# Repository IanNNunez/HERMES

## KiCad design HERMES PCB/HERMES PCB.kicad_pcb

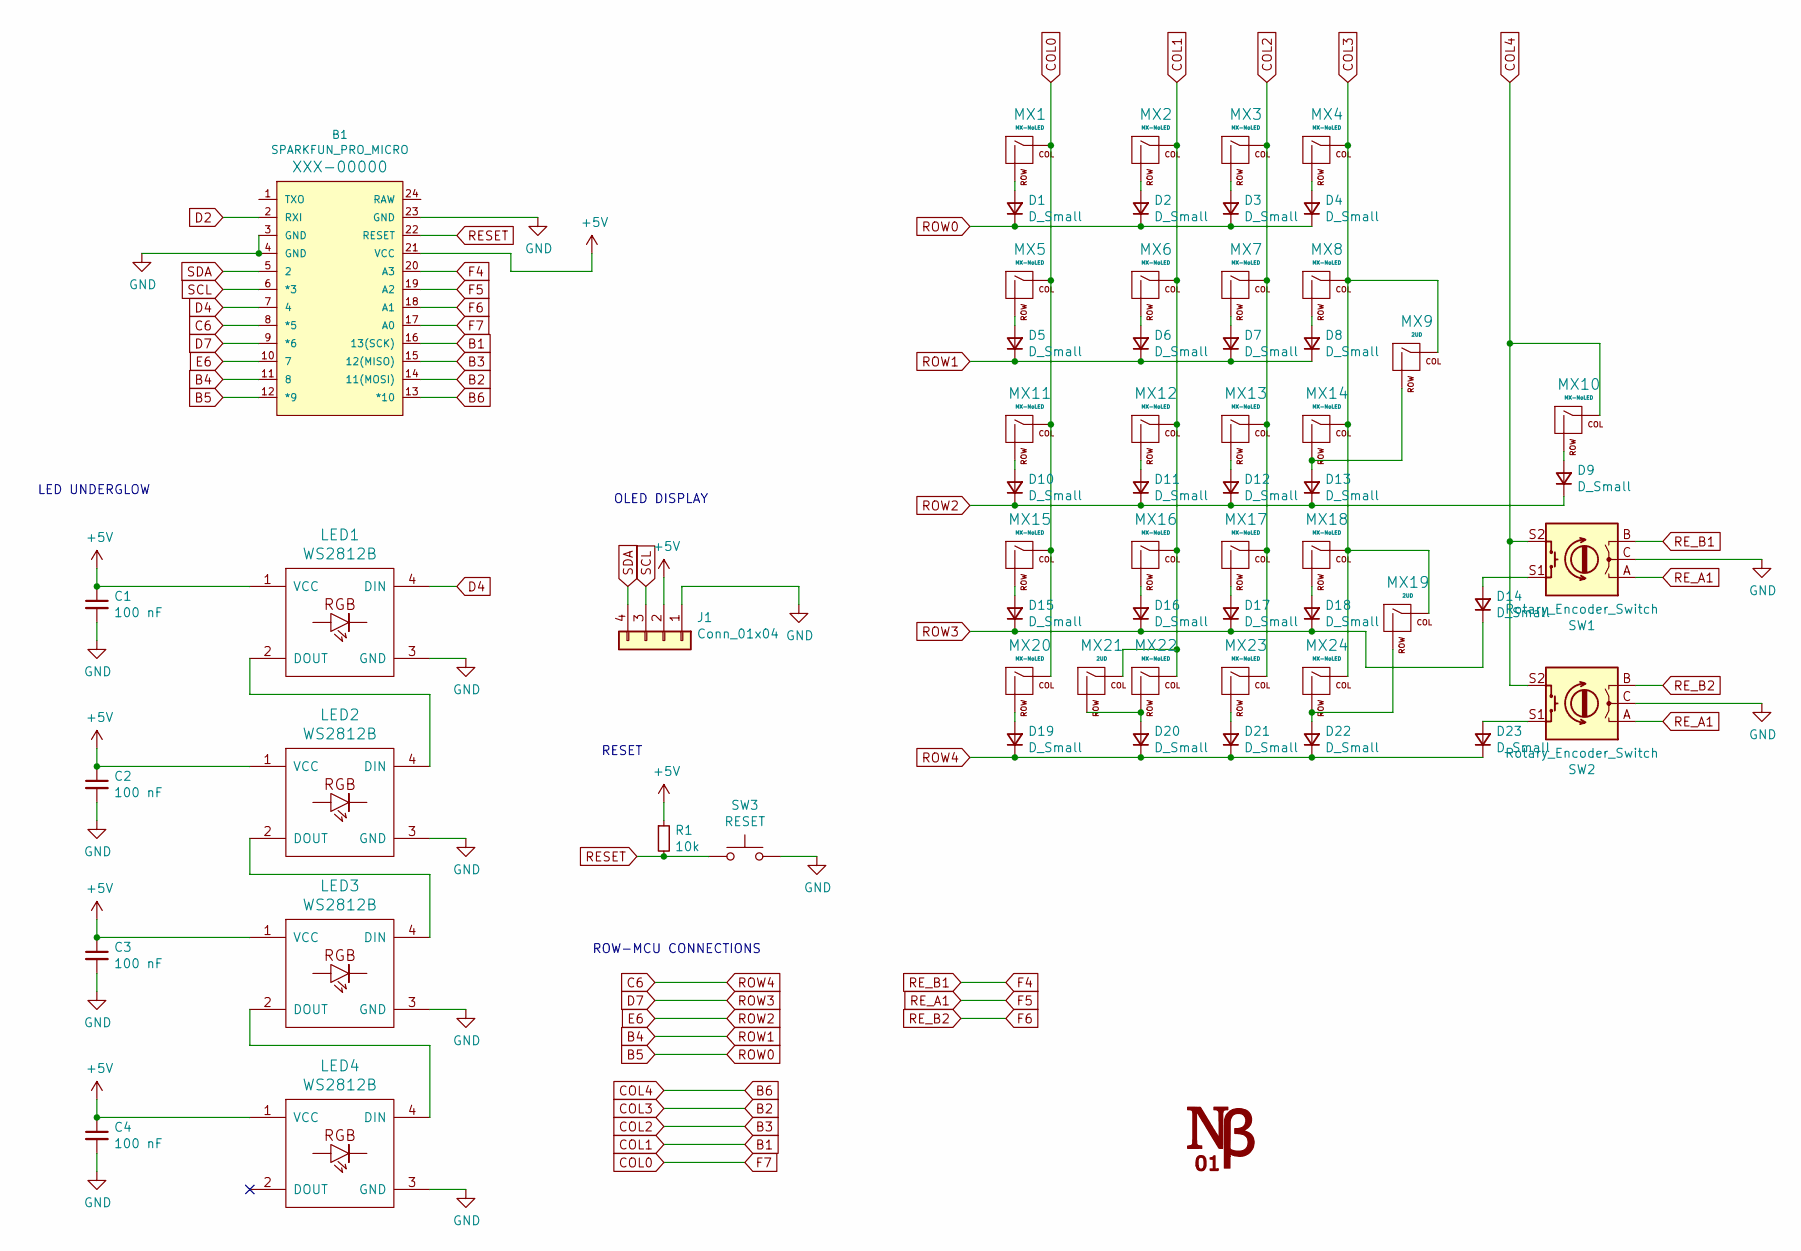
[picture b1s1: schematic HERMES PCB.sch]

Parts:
B1: SPARKFUN_PRO_MICRO
C1, C2, C3, C4: 100 nF; C_Disc_D3.0mm_W1.6mm_P2.50mm
D1, D2, D3, D4, D5, D6, D7, D8, D9, D10, D11, D12, D13, D14, D15, D16, D17, D18, D19, D20, D21, D22, D23: D_Small; D_DO-35_SOD27_P7.62mm_Horizontal
J1: Conn_01x04; PinHeader_1x04_P1.00mm_Vertical
LED1, LED2, LED3, LED4: WS2812B; LED_WS2812B_PLCC4_5.0x5.0mm_P3.2mm
MX1, MX2, MX3, MX4, MX5, MX6, MX7, MX8, MX10, MX11, MX12, MX13, MX14, MX15, MX16, MX17, MX18, MX20, MX22, MX23, MX24: MX-NoLED; MXOnly-1U-NoLED
MX9, MX19, MX21: 2UD; MXOnly-1U-NoLED
R1: 10k; R_Axial_DIN0204_L3.6mm_D1.6mm_P7.62mm_Horizontal
SW1, SW2: Rotary_Encoder_Switch; RotaryEncoder_Alps_EC11E-Switch_Vertical_H20mm
SW3: RESET; PushButton_6x6mm_TH

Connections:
+5V: B1.21 (VCC), C1.1, C2.1, C3.1, C4.1, J1.2, LED1.1 (VCC), LED2.1 (VCC), LED3.1 (VCC), LED4.1 (VCC), R1.1
B1: B1.16 (13(SCK)), MX2.1 (COL), MX6.1 (COL), MX12.1 (COL), MX16.1 (COL), MX21.1 (COL), MX22.1 (COL)
B2: B1.14 (11(MOSI)), MX4.1 (COL), MX8.1 (COL), MX9.1 (COL), MX14.1 (COL), MX18.1 (COL), MX19.1 (COL), MX24.1 (COL)
B3: B1.15 (12(MISO)), MX3.1 (COL), MX7.1 (COL), MX13.1 (COL), MX17.1 (COL), MX23.1 (COL)
B4: B1.11 (8), D5.1 (K), D6.1 (K), D7.1 (K), D8.1 (K)
B5: B1.12 (*9), D1.1 (K), D2.1 (K), D3.1 (K), D4.1 (K)
B6: B1.13 (*10), MX10.1 (COL), SW1.S2, SW2.S2
C6: B1.8 (*5), D19.1 (K), D20.1 (K), D21.1 (K), D22.1 (K), D23.1 (K)
COL0: B1.17 (A0), MX1.1 (COL), MX5.1 (COL), MX11.1 (COL), MX15.1 (COL), MX20.1 (COL)
D2: B1.2 (RXI)
D4: B1.7 (4), LED1.4 (DIN)
D7: B1.9 (*6), D14.1 (K), D15.1 (K), D16.1 (K), D17.1 (K), D18.1 (K)
E6: B1.10 (7), D9.1 (K), D10.1 (K), D11.1 (K), D12.1 (K), D13.1 (K)
F4: B1.20 (A3), SW1.B
F5: B1.19 (A2), SW1.A, SW2.A
F6: B1.18 (A1), SW2.B
GND: B1.3 (GND), B1.4 (GND), B1.23 (GND), C1.2, C2.2, C3.2, C4.2, J1.1, LED1.3 (GND), LED2.3 (GND), LED3.3 (GND), LED4.3 (GND), SW1.C, SW2.C, SW3.2
unnamed: D1.2 (A), MX1.2 (ROW)
unnamed: D2.2 (A), MX2.2 (ROW)
unnamed: D3.2 (A), MX3.2 (ROW)
unnamed: D4.2 (A), MX4.2 (ROW)
unnamed: D5.2 (A), MX5.2 (ROW)
unnamed: D6.2 (A), MX6.2 (ROW)
unnamed: D7.2 (A), MX7.2 (ROW)
unnamed: D8.2 (A), MX8.2 (ROW)
unnamed: D9.2 (A), MX10.2 (ROW)
unnamed: D10.2 (A), MX11.2 (ROW)
unnamed: D11.2 (A), MX12.2 (ROW)
unnamed: D12.2 (A), MX13.2 (ROW)
unnamed: D13.2 (A), MX9.2 (ROW), MX14.2 (ROW)
unnamed: D14.2 (A), SW1.S1
unnamed: D15.2 (A), MX15.2 (ROW)
unnamed: D16.2 (A), MX16.2 (ROW)
unnamed: D17.2 (A), MX17.2 (ROW)
unnamed: D18.2 (A), MX18.2 (ROW)
unnamed: D19.2 (A), MX20.2 (ROW)
unnamed: D20.2 (A), MX21.2 (ROW), MX22.2 (ROW)
unnamed: D21.2 (A), MX23.2 (ROW)
unnamed: D22.2 (A), MX19.2 (ROW), MX24.2 (ROW)
unnamed: D23.2 (A), SW2.S1
unnamed: LED1.2 (DOUT), LED2.4 (DIN)
unnamed: LED2.2 (DOUT), LED3.4 (DIN)
unnamed: LED3.2 (DOUT), LED4.4 (DIN)
RESET: B1.22 (RESET), R1.2, SW3.1
SCL: B1.6 (*3), J1.3
SDA: B1.5 (2), J1.4

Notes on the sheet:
LED UNDERGLOW
OLED DISPLAY
RESET
ROW-MCU CONNECTIONS

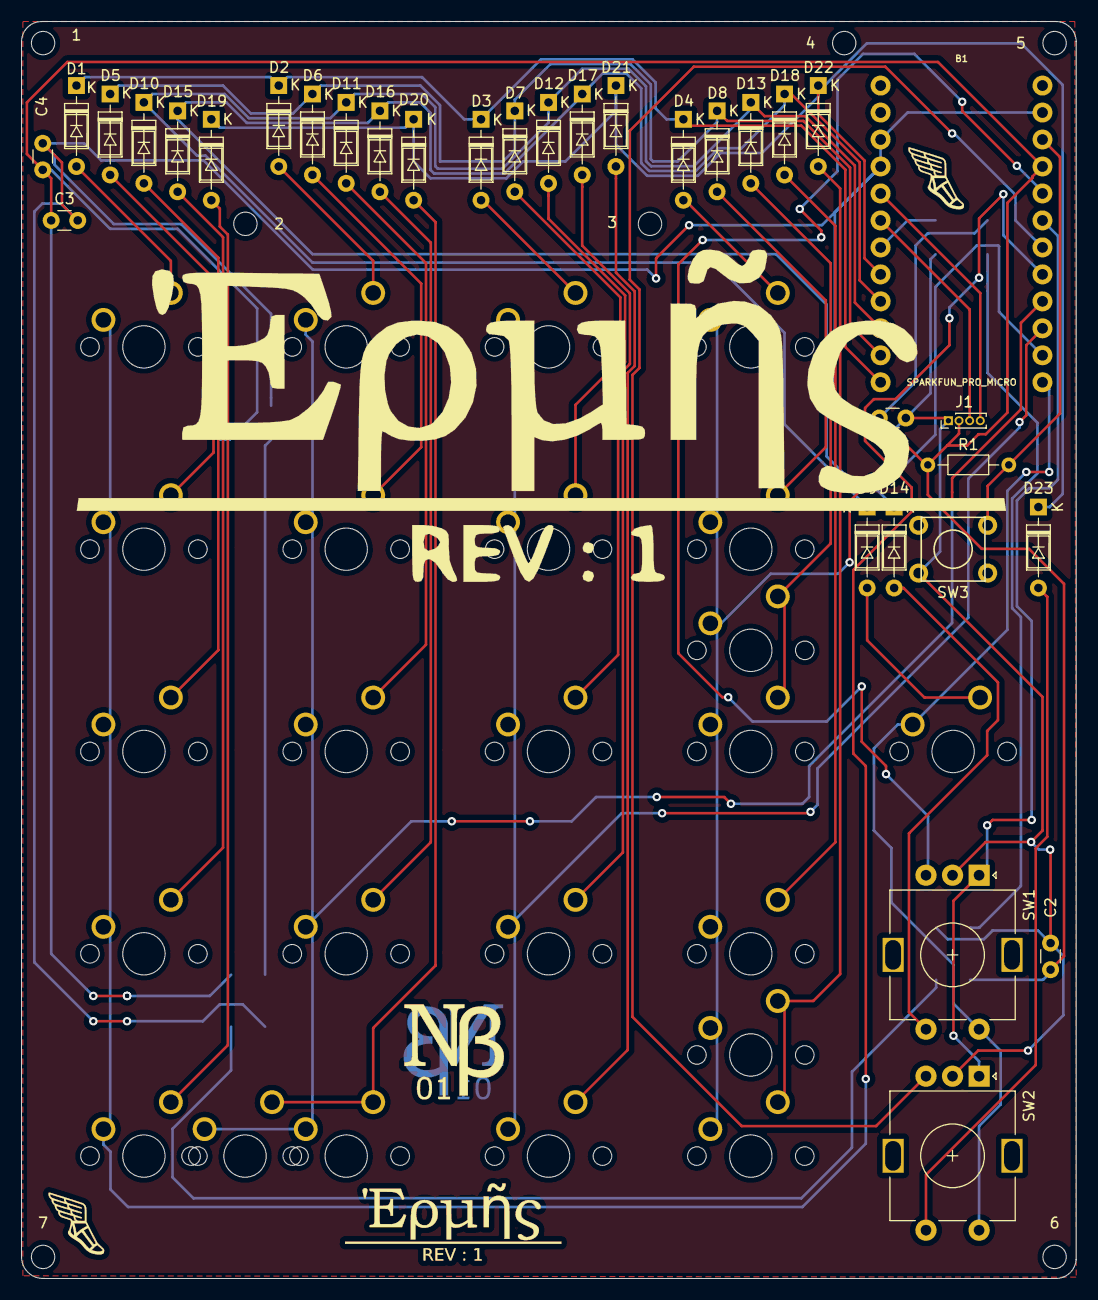
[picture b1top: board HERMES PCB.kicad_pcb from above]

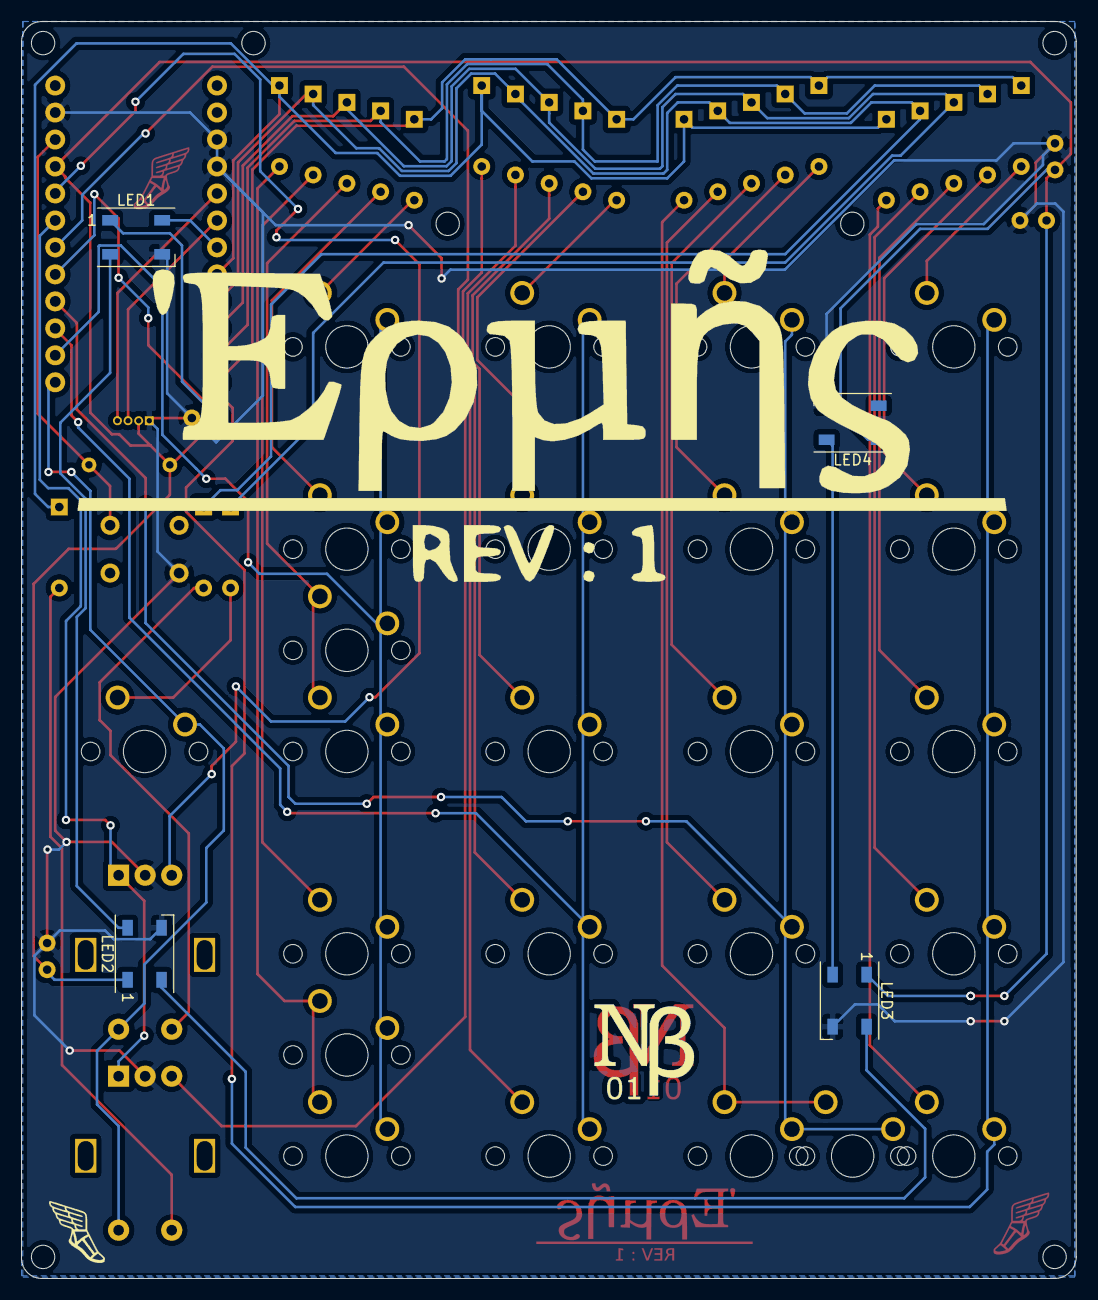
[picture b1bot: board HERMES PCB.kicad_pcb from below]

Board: 2 copper layers, 99.3 x 118.4 mm, 68 parts (4 on the bottom side), 45 nets.

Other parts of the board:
1, 2, 3, 4, 5, 6, 7: MountingHole_2.2mm_M2

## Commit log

2021-04-30 Initialized proyect
    KiCad proyect created and diagram and layout uploaded
2021-04-30 Add submodules
2021-04-30 added another submodule
2021-05-01 Schematic and PCB done
2021-05-01 Correction
2021-05-01 Added logos and tested conections
2021-05-02 Gerber and drills created
2021-05-15 started creating a rough firmaware
    Numpad and macro layout made, rgb and oled display started with Hermes logo on oled display. It is needed to configure an interface stating layer, caps, rgb state and maybe more info on the oled disp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
2021-05-16 OLED GUI and RGB in progress.
    Need to finish the different animation effects and perhaps add a led on or off warn
2021-05-16 Firmware updated
    The firmware is almost done, only needed are rotary encoders to test and program and different macro and function layouts for the keyboard
2021-05-21 Encoders made into the firmware
2021-05-21 Plate updated
2021-05-23 Updated pcb and plate designs, added led difusion layer to chasis
2021-06-03 minnor changes
2022-02-15 Added readme
